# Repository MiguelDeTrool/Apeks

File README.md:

# Apeks

Apeks is a DIY 12-bit through-hole adaptation of Mutable Instruments Peaks. Peaks was discontinued in 2017, but it's still pretty useful, and you can still see it in modern racks. For a starter system, it offers lots of functionality, so we made a version that's cheap and easy to fabricate, build, and modify.

## Hardware:
We saw what sound-force.nl did for Braids, and noticed Peaks used the same classic STM32 processor, so the same style of conversion could be done. Overall the conversion process was very similar to what Sound Force describes in their page about Braids: the layout is the same as it leaves space for THT components, the main PCB is shorter than 100mm, and the firmware only needs to have a few files changed (dac.h, dac.cc, lfo.h, and mini_sequencer.h).

The output stage needed to be modified slightly, as Peaks' output swing is 16V, which at 12 bits means the resolution would only be at almost 4mV. That's almost 5 cents at 1V/Oct, which is too much, as we could hear the steps in the output.

This version uses a 12 bit DAC, and the output op-amps scale the output to +/- 5V. This allows for a resolution of around 2.44mV, which we find acceptable for non-pitch related modulation.

## Firmware
For the DAC, the dac.h file is modified to bitshift the 16 bit values by 4 bits. The SPI output message use masks according to the MCP4822 write commands.

To bring the LFOs and mini-sequencers up to the maximum level (if not, they would be at around +/-3.125V), a couple of changes are needed. The lfo.h set_level arguments need to be set to 65535 instead of 40960, and in the output line of mini_sequencer.h, the same number needs to be changed.

The firmware is available as source and pre-compiled. We used a CP2102 and STM32CubeProg to program the chip (see images for a wiring diagram).

When you use the module for the first time, flash the bootloader and the main firmware. Then take care to calibrate it according to [these instructions](https://forum.mutable-instruments.net/t/trimpots-versus-software-calibration-of-peaks/8213/2).

## Panel
There are two panel versions. One uses 6mm caps for the trigger buttons, with LEDs that shine through the PCB beside them. The other has 8mm holes for the original illuminated buttons.
*Note: We've only tried our prototype panels for now, we haven't had these panels fabricated yet.*

## Further modifications
This version stays as close as possible to the original, but we'd be excited to see further modifications and improvements. We're working on a 64kb firmware (no easter egg and smaller bootloader), and a Dead Man's Catch adaptation.

But why not try to add CV inputs with attenuverters for the pots, make an SMD micro version that can be pre-fabbed, use an adapter board to use another DAC, see if you can do the same for Tides v1 etc...

## Build notes
We've included a BOM with links to Tayda, where you can source almost all the parts quite cheaply. The BOM includes some helpful notes about some components.

It's very hard to get ahold of boards with genuine STM32 chips right now. We haven't tested this with any other versions, like APM32, GD32, CH32 etc... but we can only assume that they will work too. **Just be careful that the pinouts match!**

## Contact
This is a DIY project, with no instructions or build support. However, I can try to answer some questions you may have (if I have the time) at [migueldetrool@protonmail.com](mailto:migueldetrool@protonmail.com).

Check out [Quinie's blog and shop](https://www.quinie.nl), where there are PCB and panels for sale.

*If you get these boards or panels fabricated, please do contact me. These boards have been tested, but still, maybe I oversaw a problem, so it would be good to have confirmation that these work for others.*

### Thanks
Thanks to sound-force.nl and matias-levy for inspiration, and Emilie Gillet for the original design and helpful forum posts.

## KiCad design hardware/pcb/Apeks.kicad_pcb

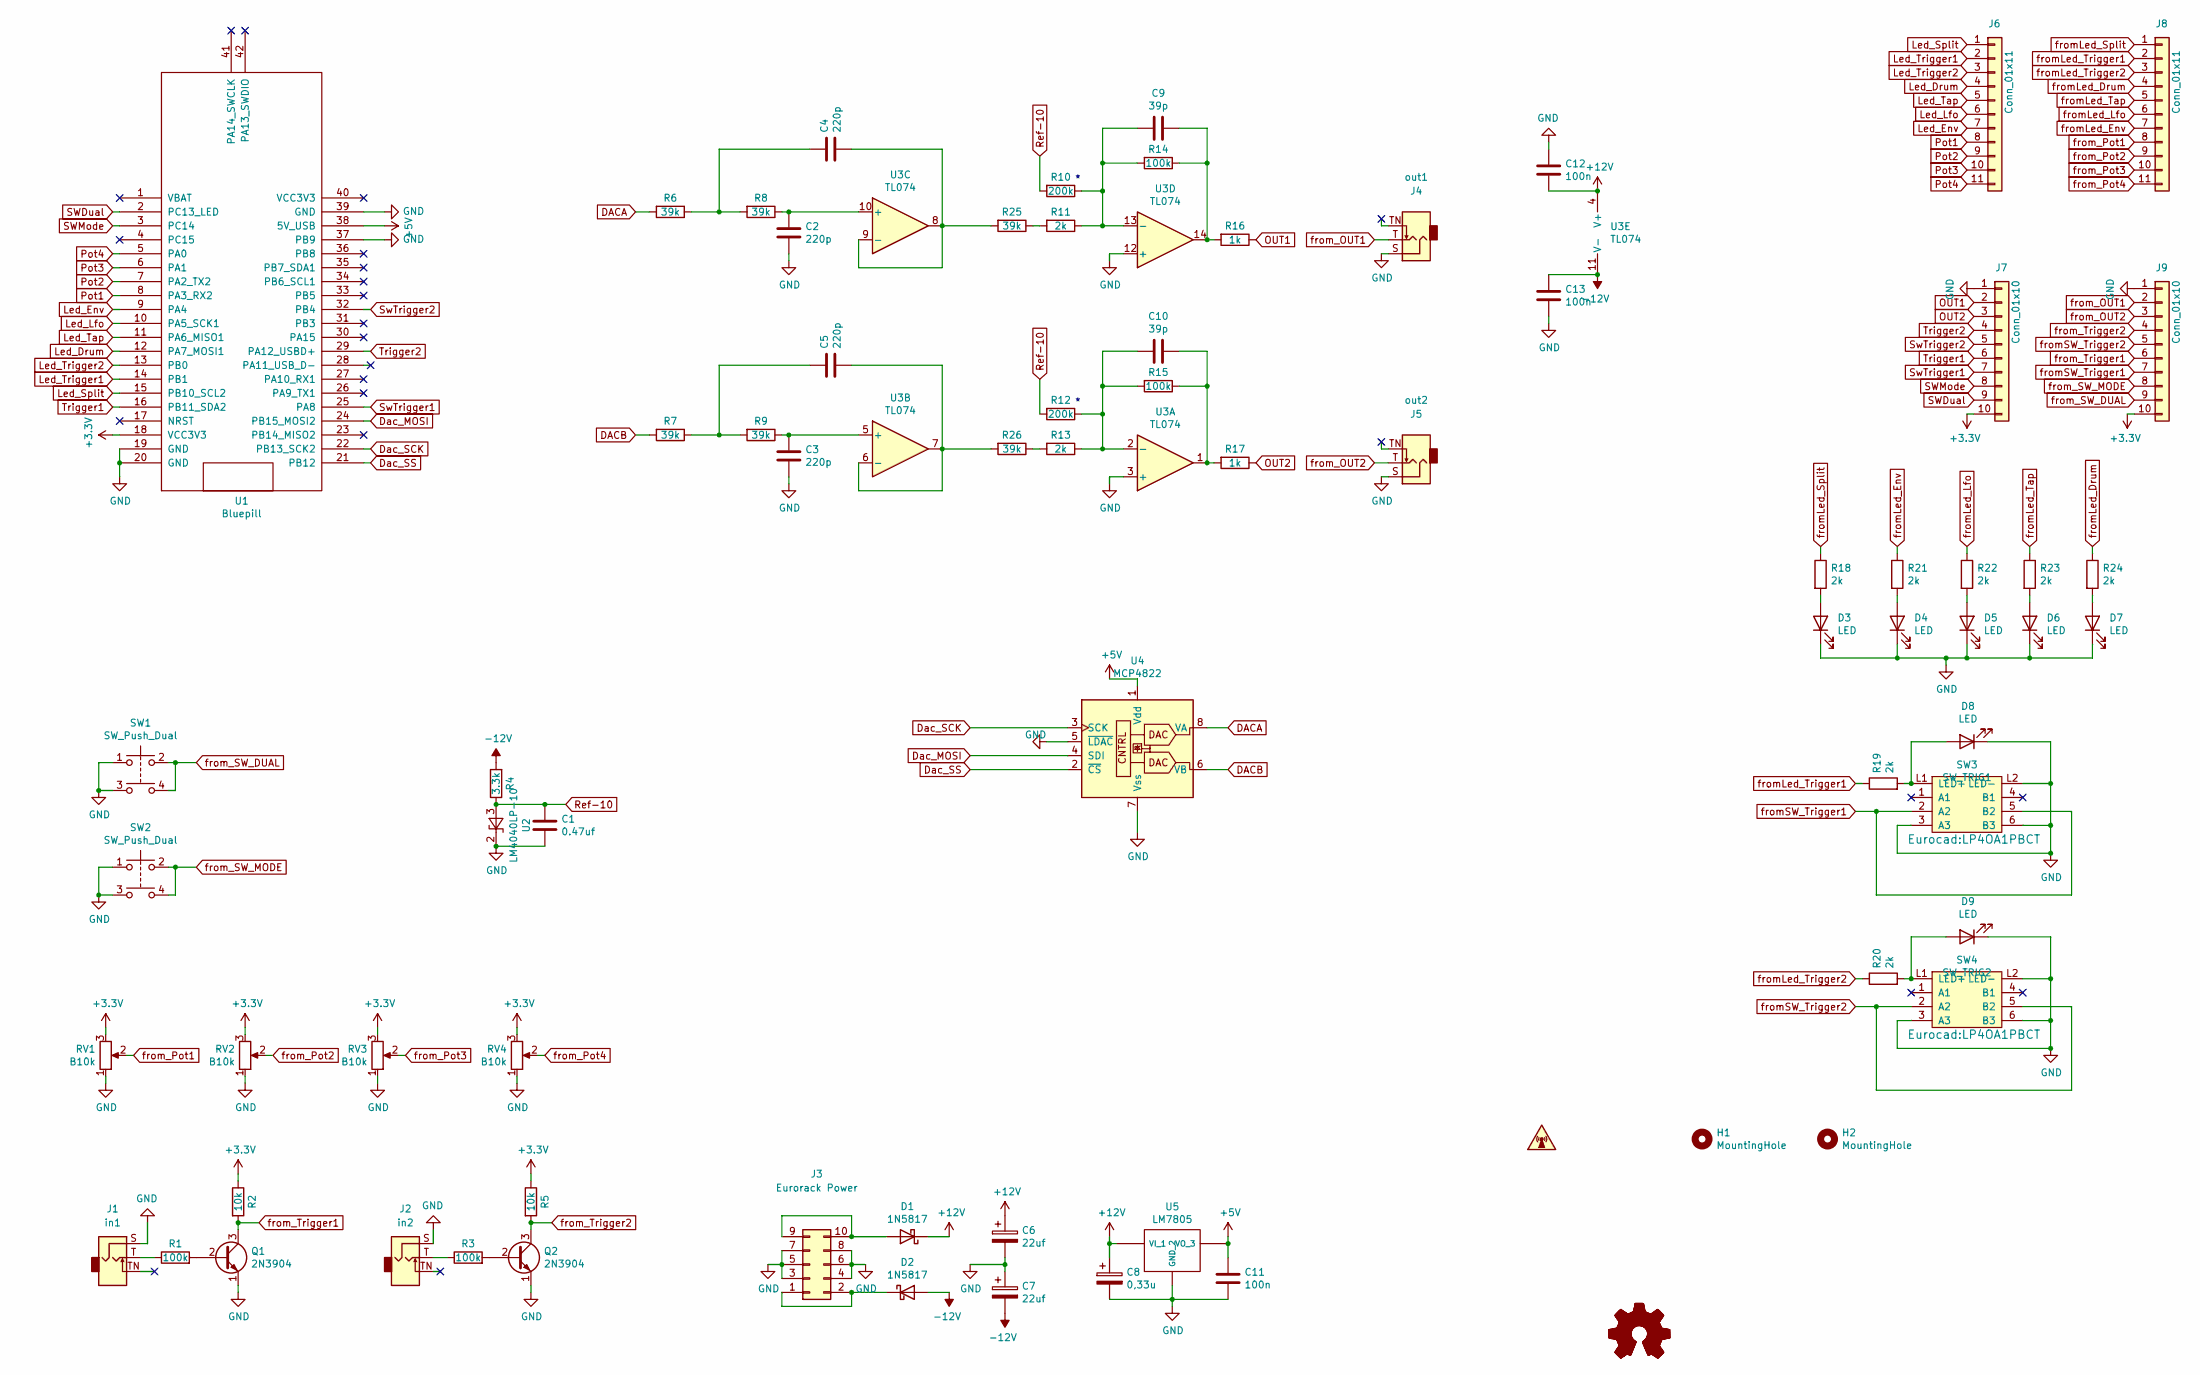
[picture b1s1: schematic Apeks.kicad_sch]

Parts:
C1: 0.47uf; C_Disc_D3.4mm_W2.1mm_P2.50mm
C2, C3, C4, C5: 220p; C_Disc_D3.4mm_W2.1mm_P2.50mm
C6, C7: 22uf; CP_Radial_D5.0mm_P2.50mm
C8: 0,33u; CP_Radial_D5.0mm_P2.50mm
C9, C10: 39p; C_Disc_D3.4mm_W2.1mm_P2.50mm
C11, C12, C13: 100n; C_Disc_D3.4mm_W2.1mm_P2.50mm
D1, D2: 1N5817; D_DO-41_SOD81_P10.16mm_Horizontal
D3, D4, D5, D6, D7, D8, D9: LED; LED_D3.0mm
H1, H2: MountingHole; MountingHole_3.2mm_M3
J1: in1; Jack_3.5mm_QingPu_WQP-PJ398SM_Vertical_CircularHoles
J2: in2; Jack_3.5mm_QingPu_WQP-PJ398SM_Vertical_CircularHoles
J3: Eurorack Power; IDC-Header_2x05_P2.54mm_Vertical
J4: out1; Jack_3.5mm_QingPu_WQP-PJ398SM_Vertical_CircularHoles
J5: out2; Jack_3.5mm_QingPu_WQP-PJ398SM_Vertical_CircularHoles
J6: Conn_01x11; PinHeader_1x14_P2.54mm_Vertical
J7: Conn_01x10; PinHeader_1x07_P2.54mm_Vertical
J8: Conn_01x11; PinSocket_1x14_P2.54mm_Vertical
J9: Conn_01x10; PinSocket_1x07_P2.54mm_Vertical
Q1, Q2: 2N3904; TO-92_Inline
R1, R3, R14, R15: 100k; R_Axial_DIN0204_L3.6mm_D1.6mm_P7.62mm_Horizontal
R2, R5: 10k; R_Axial_DIN0204_L3.6mm_D1.6mm_P7.62mm_Horizontal
R4: 3.3k; R_Axial_DIN0204_L3.6mm_D1.6mm_P7.62mm_Horizontal
R6, R7, R8, R9, R25, R26: 39k; R_Axial_DIN0204_L3.6mm_D1.6mm_P7.62mm_Horizontal
R10, R12: 200k; R_Axial_DIN0204_L3.6mm_D1.6mm_P7.62mm_Horizontal
R11, R13, R18, R19, R20, R21, R22, R23, R24: 2k; R_Axial_DIN0204_L3.6mm_D1.6mm_P7.62mm_Horizontal
R16, R17: 1k; R_Axial_DIN0204_L3.6mm_D1.6mm_P7.62mm_Horizontal
RV1, RV2, RV3, RV4: B10k; Potentiometer_Alps_RK09K_Single_Vertical
SW1, SW2: SW_Push_Dual; SW_PUSH_6mm
SW3: SW_TRIG1; LP4OA1PBCT
SW4: SW_TRIG2; LP4OA1PBCT
U1: Bluepill; BluePill_STM32F103C
U2: LM4040LP-10; TO-92_Inline
U3: TL074; DIP-14_W7.62mm_Socket_LongPads
U4: MCP4822; DIP-8_W7.62mm
U5: LM7805; TO-220-3_Horizontal_TabDown

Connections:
+3V3: J7.10, J9.10, R2.1, R5.1, RV1.3, RV2.3, RV3.3, RV4.3, U1.18 (VCC3V3)
+5V: C11.1, U1.38 (5V_USB), U4.1 (Vdd), U5.3 (VO)
+12V: C6.1, C8.1, C12.2, D1.1 (K), U3.4 (V+), U5.1 (VI)
-12V: C7.2, C13.1, D2.2 (A), R4.2, U3.11 (V-)
DACA: R6.2, U4.8 (VA)
DACB: R7.2, U4.6 (VB)
Dac_MOSI: U1.24 (PB15_MOSI2), U4.4 (SDI)
Dac_SCK: U1.22 (PB13_SCK2), U4.3 (SCK)
Dac_SS: U1.21 (PB12), U4.2 (~CS)
GND: C1.2, C2.2, C3.2, C6.2, C7.1, C8.2, C11.2, C12.1, C13.2, D3.1 (K), D4.1 (K), D5.1 (K), D6.1 (K), D7.1 (K), D8.1 (K), D9.1 (K), J1.S, J2.S, J3.3, J3.4, J3.5, J3.6, J3.7, J3.8, J4.S, J5.S, J7.1, J9.1, Q1.1 (E), Q2.1 (E), RV1.1, RV2.1, RV3.1, RV4.1, SW1.1, SW1.3, SW2.1, SW2.3, SW3.3 (A3), SW3.6 (B3), SW3.L2 (LED-), SW4.3 (A3), SW4.6 (B3), SW4.L2 (LED-), U1.19 (GND), U1.20 (GND), U1.37 (PB9), U1.39 (GND), U2.2 (K), U3.3 (+), U3.12 (+), U4.5 (~LDAC), U4.7 (Vss), U5.2 (GND)
Led_Drum: J6.4, U1.12 (PA7_MOSI1)
Led_Env: J6.7, U1.9 (PA4)
Led_Lfo: J6.6, U1.10 (PA5_SCK1)
Led_Split: J6.1, U1.15 (PB10_SCL2)
Led_Tap: J6.5, U1.11 (PA6_MISO1)
Led_Trigger1: J6.2, U1.14 (PB1)
Led_Trigger2: J6.3, U1.13 (PB0)
unnamed: C2.1, R8.1, U3.10 (+)
unnamed: C3.1, R9.1, U3.5 (+)
unnamed: C4.1, R6.1, R8.2
unnamed: C4.2, R25.2, U3.8, U3.9 (-)
unnamed: C5.1, R7.1, R9.2
unnamed: C5.2, R26.2, U3.6 (-), U3.7
unnamed: C9.1, R10.1, R11.1, R14.2, U3.13 (-)
unnamed: C9.2, R14.1, R16.2, U3.14
unnamed: C10.1, R12.1, R13.1, R15.2, U3.2 (-)
unnamed: C10.2, R15.1, R17.2, U3.1
unnamed: D1.2 (A), J3.9, J3.10
unnamed: D2.1 (K), J3.1, J3.2
unnamed: D3.2 (A), R18.2
unnamed: D4.2 (A), R21.2
unnamed: D5.2 (A), R22.2
unnamed: D6.2 (A), R23.2
unnamed: D7.2 (A), R24.2
unnamed: D8.2 (A), R19.2, SW3.L1 (LED+)
unnamed: D9.2 (A), R20.2, SW4.L1 (LED+)
unnamed: J1.T, R1.1
unnamed: J2.T, R3.1
unnamed: Q1.2 (B), R1.2
unnamed: Q2.2 (B), R3.2
unnamed: R11.2, R25.1
unnamed: R13.2, R26.1
OUT1: J7.2, R16.1
OUT2: J7.3, R17.1
Pot1: J6.8, U1.8 (PA3_RX2)
Pot2: J6.9, U1.7 (PA2_TX2)
Pot3: J6.10, U1.6 (PA1)
Pot4: J6.11, U1.5 (PA0)
Ref-10: C1.1, R4.1, R10.2, R12.2, U2.3 (A)
SWDual: J7.9, U1.2 (PC13_LED)
SWMode: J7.8, U1.3 (PC14)
SwTrigger1: J7.7, U1.25 (PA8)
SwTrigger2: J7.5, U1.32 (PB4)
Trigger1: J7.6, U1.16 (PB11_SDA2)
Trigger2: J7.4, U1.29 (PA12_USBD+)
fromLed_Drum: J8.4, R24.1
fromLed_Env: J8.7, R21.1
fromLed_Lfo: J8.6, R22.1
fromLed_Split: J8.1, R18.1
fromLed_Tap: J8.5, R23.1
fromLed_Trigger1: J8.2, R19.1
fromLed_Trigger2: J8.3, R20.1
fromSW_Trigger1: J9.7, SW3.2 (A2), SW3.5 (B2)
fromSW_Trigger2: J9.5, SW4.2 (A2), SW4.5 (B2)
from_OUT1: J4.T, J9.2
from_OUT2: J5.T, J9.3
from_Pot1: J8.8, RV1.2
from_Pot2: J8.9, RV2.2
from_Pot3: J8.10, RV3.2
from_Pot4: J8.11, RV4.2
from_SW_DUAL: J9.9, SW1.2, SW1.4
from_SW_MODE: J9.8, SW2.2, SW2.4
from_Trigger1: J9.6, Q1.3 (C), R2.2
from_Trigger2: J9.4, Q2.3 (C), R5.2

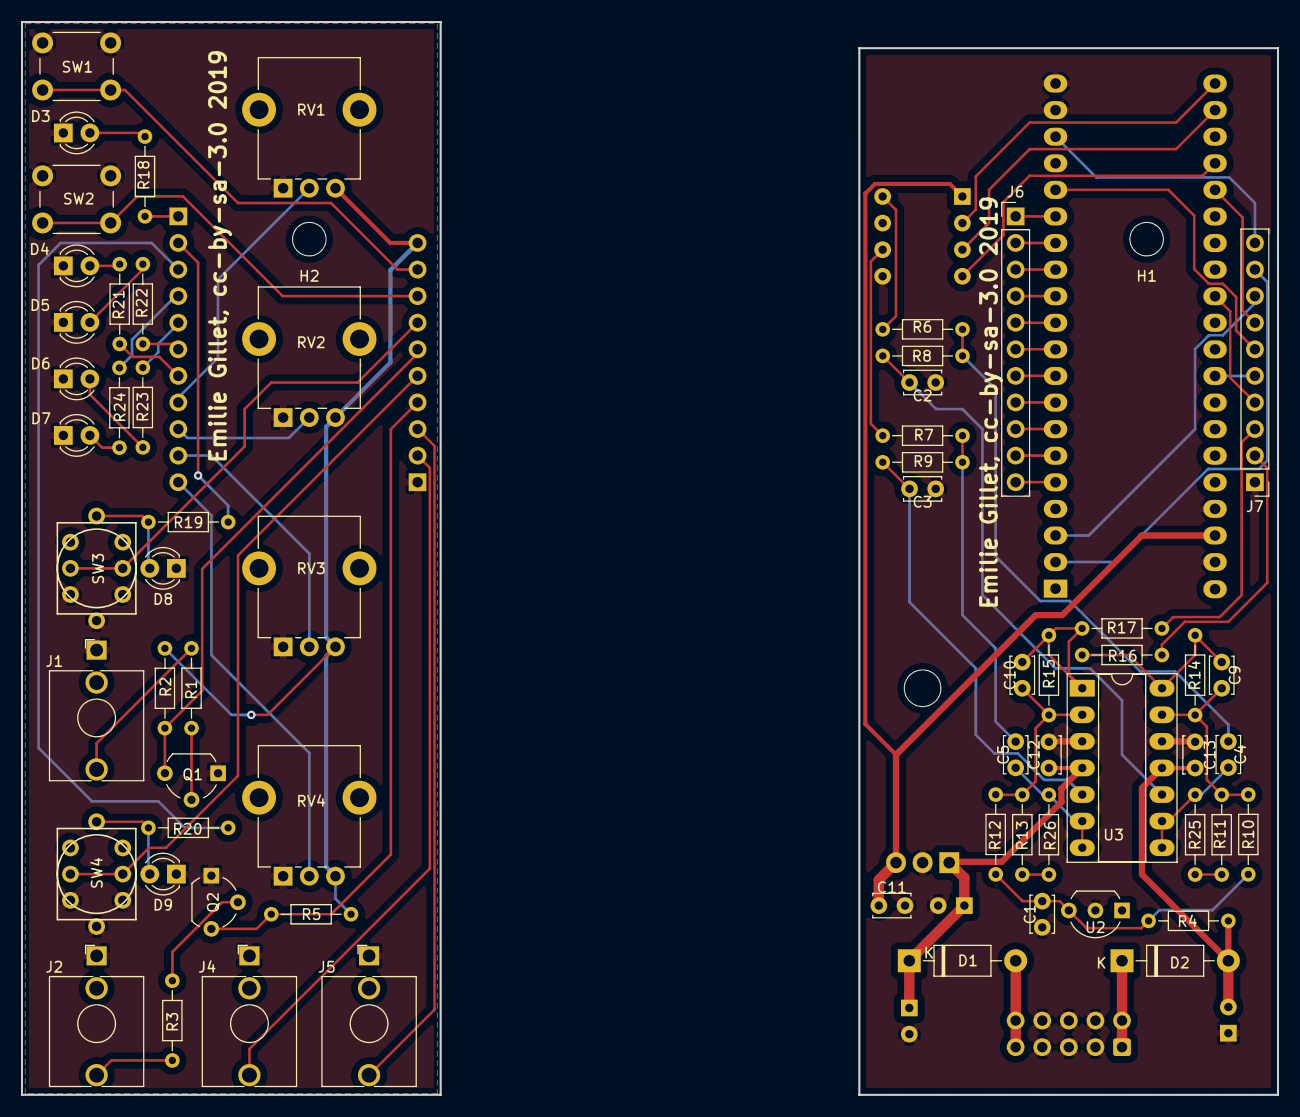
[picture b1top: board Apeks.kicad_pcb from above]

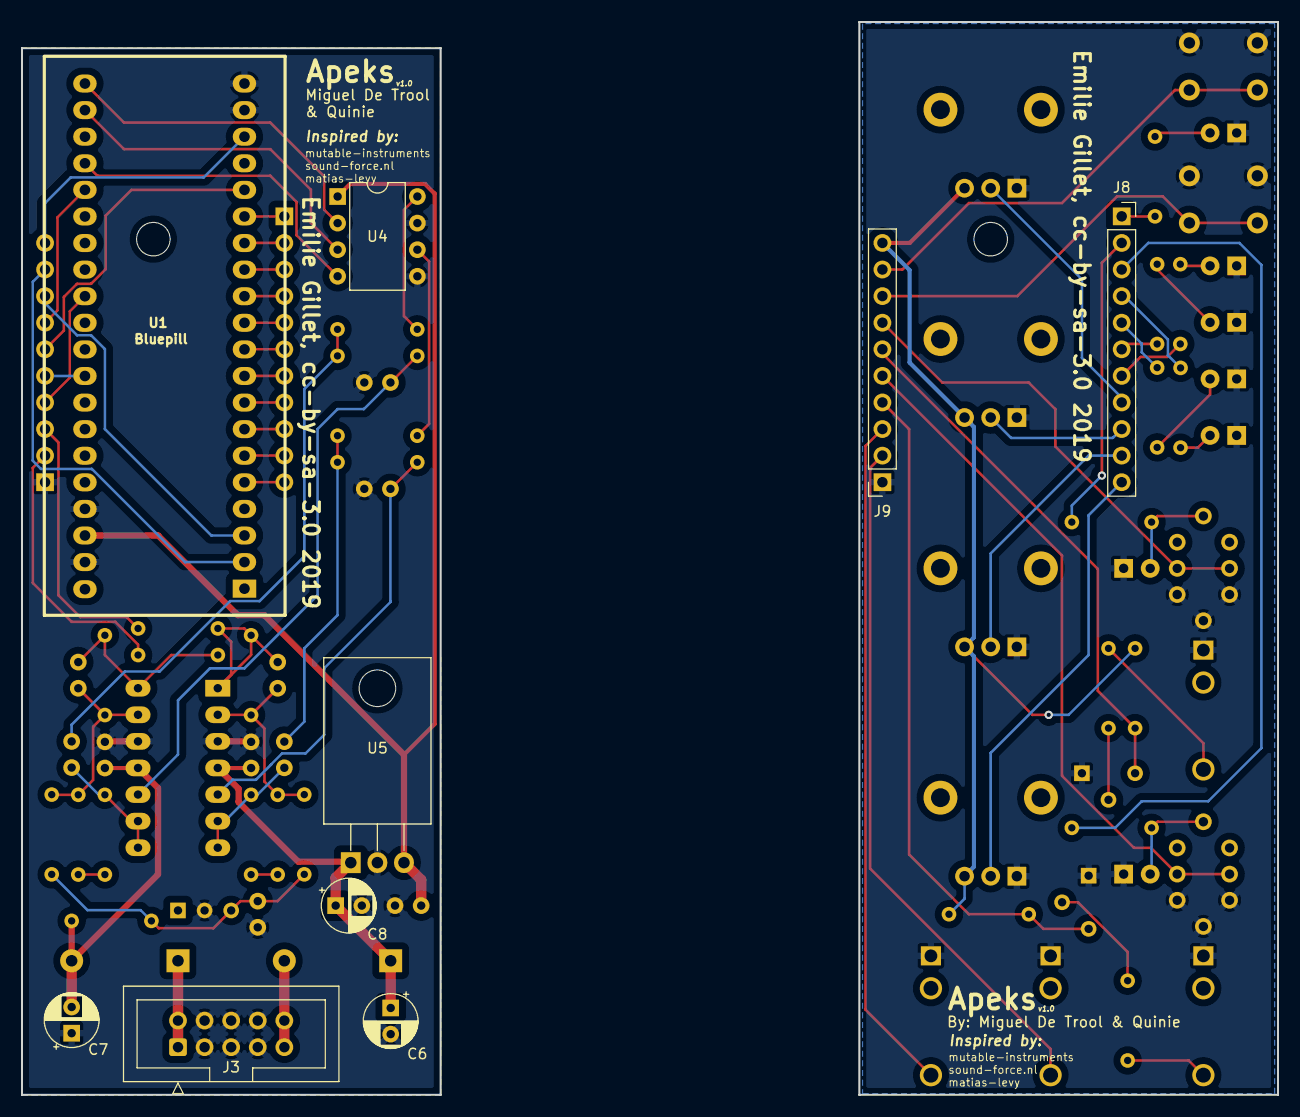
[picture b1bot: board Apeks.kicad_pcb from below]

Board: 2 copper layers, 120.0 x 102.5 mm, 74 parts (9 on the bottom side), 74 nets.

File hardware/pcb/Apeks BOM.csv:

Designator,Description,Quantity,Designation,Link,Notes
C1,C_Disc_D3.4mm_W2.1mm_P2.50mm,1,0.47uf,https://www.taydaelectronics.com/capacitors/ceramic-disc-cap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,Same link for all ceramic capacitors
"C11,C12,C13",C_Disc_D3.4mm_W2.1mm_P2.50mm,3,100n,,
"C4,C2,C3,C5",C_Disc_D3.4mm_W2.1mm_P2.50mm,4,220p,,
"C6,C7",CP_Radial_D5.0mm_P2.50mm,2,22uf,https://www.taydaelectronics.com/22uf-25v-85c-radial-electro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,
C8,CP_Radial_D5.0mm_P2.50mm,1,"0,33u",https://www.taydaelectronics.com/0-33-uf-50v-85c-radial-elec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,
"C9,C10",C_Disc_D3.4mm_W2.1mm_P2.50mm,2,39p,,
"D1,D2",D_DO-41_SOD81_P10.16mm_Horizontal,2,1N5817,https://www.taydaelectronics.com/1n5817-diode-schottky-1a-20v.html,1N5819 is actually cheaper
"D3,D4,D5,D6,D7,D8,D9",LED_D3.0mm,7,LED,https://www.taydaelectronics.com/led-3mm-green.html,"Depending on what LEDs you get, they might be too bright and you’ll need bigger resistors for them"
J1,Jack_3.5mm_QingPu_WQP-PJ398SM_Vertical_CircularHoles,1,in1,https://www.taydaelectronics.com/pj-3001f-3-5-mm-mono-phone-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,Same link for all jacks
J2,Jack_3.5mm_QingPu_WQP-PJ398SM_Vertical_CircularHoles,1,in2,,
J3,IDC-Header_2x05_P2.54mm_Vertical,1,Eurorack Power,https://www.taydaelectronics.com/10-pin-box-header-connector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,
J4,Jack_3.5mm_QingPu_WQP-PJ398SM_Vertical_CircularHoles,1,out1,,
J5,Jack_3.5mm_QingPu_WQP-PJ398SM_Vertical_CircularHoles,1,out2,,
J6,PinHeader_1x11_P2.54mm_Vertical,1,Conn_01x11,https://www.taydaelectronics.com/40-pin-2-54-mm-single-row-p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,Cut down to size
J7,PinHeader_1x10_P2.54mm_Vertical,1,Conn_01x10,https://www.taydaelectronics.com/40-pin-2-54-mm-single-row-f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,Cut down to size
J8,PinSocket_1x11_P2.54mm_Vertical,1,Conn_01x11,,
J9,PinSocket_1x10_P2.54mm_Vertical,1,Conn_01x10,,
"Q1,Q2",TO-92_Wide,2,2N3904,https://www.taydaelectronics.com/2n3904-npn-general-propose-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,
"R1,R3,R14,R15",R_Axial_DIN0204_L3.6mm_D1.6mm_P7.62mm_Horizontal,4,100k,https://www.taydaelectronics.com/resistors/1-4w-metal-film-r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,Same link for all resistors
"R10,R12",R_Axial_DIN0204_L3.6mm_D1.6mm_P7.62mm_Horizontal,2,200k,,
"R11,R18,R21,R22,R23,R24,R19,R20,R13",R_Axial_DIN0204_L3.6mm_D1.6mm_P7.62mm_Horizontal,9,2k,,
"R16,R17",R_Axial_DIN0204_L3.6mm_D1.6mm_P7.62mm_Horizontal,2,1k,,
"R2,R5",R_Axial_DIN0204_L3.6mm_D1.6mm_P7.62mm_Horizontal,2,10k,,
R4,R_Axial_DIN0204_L3.6mm_D1.6mm_P7.62mm_Horizontal,1,3.3k,,
"R6,R7,R8,R9,R25,R26",R_Axial_DIN0204_L3.6mm_D1.6mm_P7.62mm_Horizontal,6,39k,,
"RV1,RV2,RV3,RV4",Potentiometer_Alpha_RD901F-40-00D_Single_Vertical_CircularHoles,4,B10k,https://www.taydaelectronics.com/tayda-10k-ohm-linear-taper-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,
"SW1,SW2",SW_PUSH_6mm,2,SW_Push_Dual,https://www.aliexpress.com/item/32726374514.html,"Ideally, you want 6*6mm tact switches with square heads, that will fit the cap nicely. If you want to only order from tayda, you can probably force the cap onto a round head switch, like this https://www.taydaelectronics.com/tact-switch-6-6mm-7-3mm-thr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"
SW3,LP4OA1PBCT,1,SW_TRIG1,https://www.taydaelectronics.com/push-button-switch-momentar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,"For the original illuminated buttons with 8mm head, you can get these ones https://www.aliexpress.com/item/4000415375387.html?gatewayAd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"
SW4,LP4OA1PBCT,1,SW_TRIG2,,"Depending on which buttons you use, you may have to do some light re-wiring by adding jumpers between certain pins. On the board, the two middle pins need to connect to the two bottom pins when the button is pressed."
U1,BluePill_STM32F103C,1,Bluepill,,"Needs STM32F103CBT6 version, with 128kb memory. You can only get clones of these currently. I’m working on a smaller version of firmware to work on 64kb."
U2,TO-92_Inline_Wide,1,LM4040LP-10,,"Not common on ali sites, since the output is not v/oct, it’s easiest to just replace it with a zener like this: https://www.taydaelectronics.com/1n4740a-1n4740-zener-diode-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"
U3,DIP-14_W7.62mm_Socket_LongPads,1,TL074,https://www.taydaelectronics.com/tl074-quad-operational-ampl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,
U4,DIP-8_W7.62mm,1,MCP4822,,"Can be found on ali sites, like here: https://www.aliexpress.com/item/33020375029.html"
U5,TO-220-3_Horizontal_TabDown,1,LM7805,https://www.taydaelectronics.com/lm7805-l7805-7805-voltage-r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,
,,,,,
Extras,,,,,
,STM32 Blue Pill headers,2,,https://www.taydaelectronics.com/20-pin-2-54-mm-single-row-f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,"Some clone boards have a 5V pin at the top right, instead of the usual ground. Cut the pin off if it has 5V."
,Tactile switch caps,2,,https://www.taydaelectronics.com/push-button-switch-caps-bla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,
,"Push button caps, for 6mm version",2,,https://www.taydaelectronics.com/push-button-switch-caps-bla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,
,Potentiometer knobs,4,,https://www.taydaelectronics.com/knob-davies-1900h-clone-black.html,
,14 pin socket,1,,https://www.taydaelectronics.com/14-pin-dip-ic-socket-adapto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,
,8 pin socket,1,,https://www.taydaelectronics.com/8-pin-dip-ic-socket-adaptor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,

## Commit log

2022-12-11 Add firmware source code
2023-02-09 Add switched channels minified firmware
2023-02-09 Switch channel files

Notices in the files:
hardware/pcb/Apeks.kicad_pcb:
Emilie Gillet, cc-by-sa-3.0 2019
